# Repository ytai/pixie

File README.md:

# Pixie
Design files for the Pixie 3W RGB LED product.

The Pixie is a 3W RGB smart LED module, designed by Ytai Ben-Tsvi and sold by Adafruit:
https://www.adafruit.com/products/2741

This is the home of its hardware design files and the firmware code.
While most users never need to worry about it, the Pixie features a PIC12F MCU, which can be reprogrammed for changing its behavior.

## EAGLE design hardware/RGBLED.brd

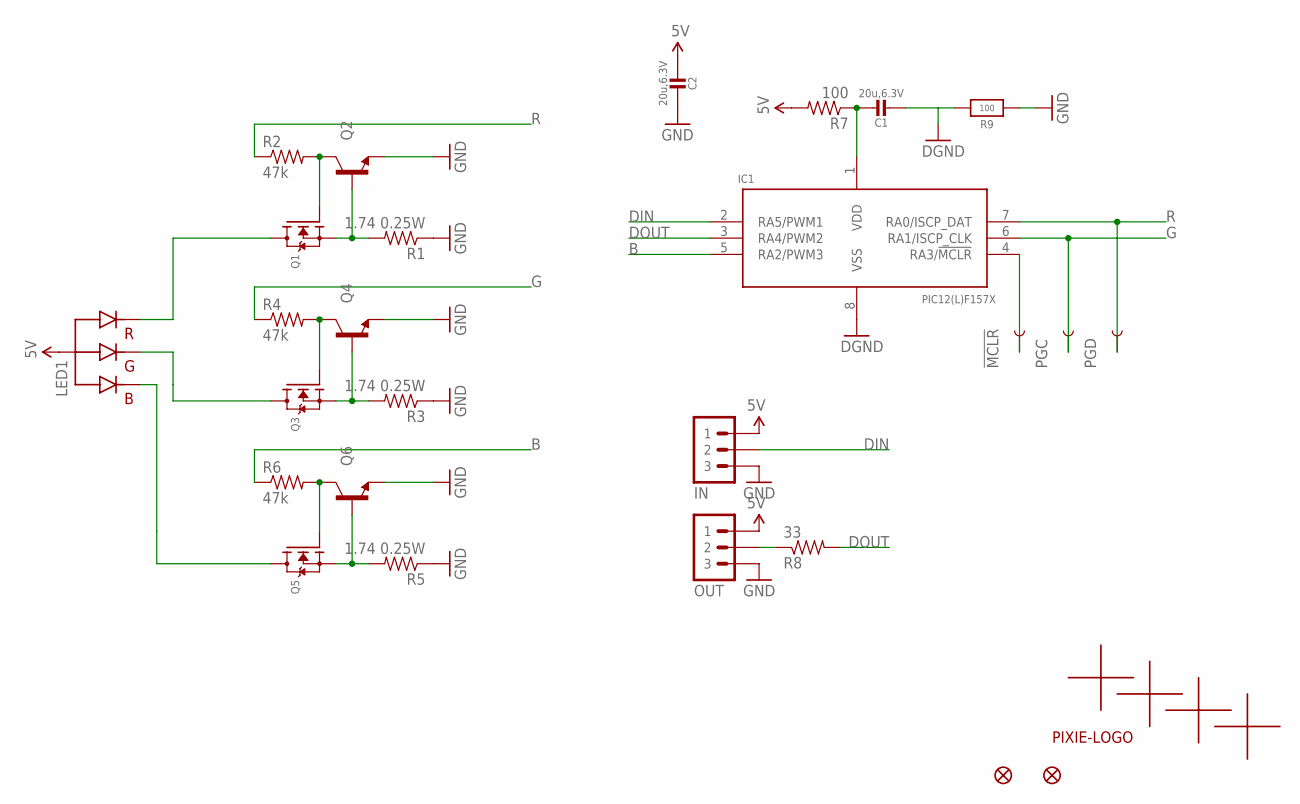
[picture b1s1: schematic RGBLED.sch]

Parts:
!MCLR: TEST-POINT3X4; PAD.03X.04
C1, C2: 20u,6.3V; _0805MP
IC1: PIC12(L)F157X; MSOP-8
IN: M030.1PWR+SIG; 1X03-0.1PWR+SIG
LED1: RGBLED_CA; RGBLED3W4PIN
OUT: M030.1PWR+SIG; 1X03-0.1PWR+SIG
PGC: TEST-POINT3X4; PAD.03X.04
PGD: TEST-POINT3X4; PAD.03X.04
Q1, Q3, Q5: IRLML2060TRPBF; SOT23-3
Q2, Q4, Q6: MMBT2222A; SOT23-3
R1, R3, R5: 1.74 0.25W; 1206
R2, R4, R6: 47k; 0603-RES
R7: 100; 0603-RES
R8: 33; 0603-RES
R9: 100; _0603MP
U$1, U$2, U$3, U$4: ALIGN_CROSS
U$5: PIXIE-LOGO
U$6, U$7: FIDUCIAL""; FIDUCIAL_1MM

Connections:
5V: C2.2, IN.P$1 (1), LED1.ANODE (VCC), OUT.P$1 (1), R7.2
B: IC1.5 (RA2/PWM3), R6.1
DGND: C1.2, IC1.8 (VSS), R9.2
DIN: IC1.2 (RA5/PWM1), IN.P$2 (2)
DOUT: IC1.3 (RA4/PWM2), R8.2
G: IC1.6 (RA1/ISCP_CLK), PGC.P$1, R4.1
GND: C2.1, IN.P$3 (3), OUT.P$3 (3), Q2.2 (E), Q4.2 (E), Q6.2 (E), R1.1, R3.1, R5.1, R9.1
unnamed: LED1.R (RED), Q1.3 (D)
unnamed: LED1.G (GREEN), Q3.3 (D)
unnamed: LED1.B (BLUE), Q5.3 (D)
unnamed: Q1.2 (S), Q2.1 (B), R1.2
unnamed: Q3.2 (S), Q4.1 (B), R3.2
unnamed: OUT.P$2 (2), R8.1
unnamed: !MCLR.P$1, IC1.4 (RA3/!MCLR)
unnamed: Q5.1 (G), Q6.3 (C), R6.2
unnamed: Q3.1 (G), Q4.3 (C), R4.2
unnamed: C1.1, IC1.1 (VDD), R7.1
unnamed: Q5.2 (S), Q6.1 (B), R5.2
unnamed: Q1.1 (G), Q2.3 (C), R2.2
R: IC1.7 (RA0/ISCP_DAT), PGD.P$1, R2.1

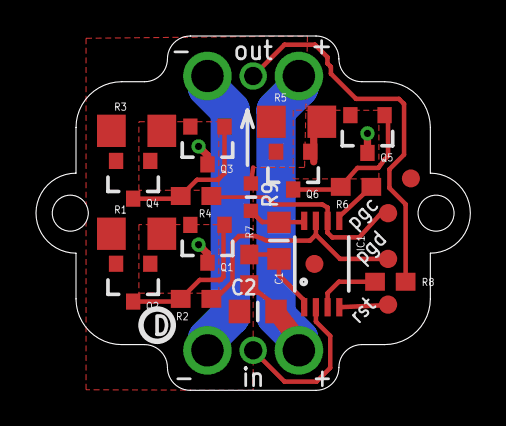
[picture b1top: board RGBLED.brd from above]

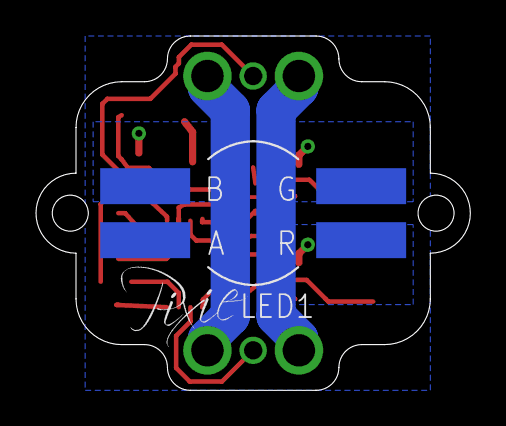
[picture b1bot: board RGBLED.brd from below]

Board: 2 copper layers, 24.1 x 19.7 mm, 32 parts (2 on the bottom side), 20 nets.

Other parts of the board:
U$8: PCBFEAT-REV-040

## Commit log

2015-10-21 Pixie v2 Bring-up
2015-10-21 Sorta workin'
2015-10-21 Things seem to work now!
2015-10-21 Rename to Pixie
2015-10-21 Improved temperature calculation
2015-10-21 Clear lingering interrupts before enabling
2015-10-21 Upon long silence, move on even if we didn't get 24 bits.
    This is important for resync.
2015-10-21 Support UART mode
2015-10-21 Cleanup
2015-10-21 Free up timer 2
    Use timer 1 instead. Timer 2 supports interrupt on match.
2015-10-21 Updated gitignore
2015-10-21 Colors were swapped
2015-10-21 Initial commit of hardware design files
2015-10-21 Temperature calibration mode
    Max temperature is stored as a user ID value and read in runtime.
    Initially, if it is unset (0xFF), we go into a mode where we spit out
    temperature readings as a 9600 8N1 serial stream over the DOUT pin.
2015-10-21 Enable pull-up and Schmidt trigger input on Din
2015-10-21 Some MPLABX BS
2015-10-21 Fix error in temperature constants
2016-04-04 Avoid watchdog reset during temperature emission
2016-04-04 Increase reference voltage conversion time
    Experiments show that the reading does not stabilize within 20us.
    50us looks a lot better.

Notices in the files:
parts and their libraries:
SparkFun-Resistors: Licensing: Creative Commons ShareAlike 4.0 International - https://creativecommons.org/licenses/by-sa/4.0
microbuilder: This work is placed in the public domain, and may be freely used for commercial and non-commercial work with the following conditions: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
